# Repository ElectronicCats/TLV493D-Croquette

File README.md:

# Electronic Cats Croquette TLV493D

The 3D magnetic sensor TLV493D-A1B6 offers accurate three-dimensional sensing with extremely low power consumption in a small 6-pin package. With its magnetic field detection in x, y, and z-direction the sensor reliably measures three-dimensional, linear and rotation movements. Applications include joysticks, control elements (white goods, multifunction knops), or electric meters (anti tampering) and any other application that requires accurate angular measurements or low power consumptions.
The integrated temperature sensor can furthermore be used for plausibility checks.

Key features are 3D magnetic sensing with a very low power consumption during operations. The sensor has a digital output via 2-wire based standard I2C interface up to 1 MBit/sec and 12 bit data resolution for each measurement direction (Bx, By and Bz linear field measurement up to +-130mT).

## Key Features and Benefits
* Integrated temperature sensing
* Low current consumption of 0.007 µA in power down mode and 10 µA in ultra low power mode
* 2.7 to 3.5 V operating supply voltage
* Digital output via 2-wire standard I2C interface
* Bx, By and Bz linear field measurement up to ±130 mT
* 12-bit data resolution for each measurement direction
* Resolution 98 µT/LSB
* Operating temperature range from -40 °C to 125 °C
* [GUI](https://www.infineon.com/dgdl/Infineon-Software-for-3D-Magnetic-Sensor-2Go%20incl.%20out-of-shaft_05_06-SW-v05_06-EN.zip?fileId=5546d4626102d35a01614626f9644e4e) for free download as well as integration in Arduino IDE with this repository

## Usage

Please see the example sketches in the repository [Arduino Library](https://github.com/Infineon/TLV493D-A1B6-3DMagnetic-Sensor) in this library to learn more about the usage of the sensor.

### Usage Electronic Cats TLV493D with Arduino Library 

The Electronic Cats TLV493D-A1B6 3DMagnetic is a standalone break out board. You can connect it easily to any microcontroller of your choice which is Arduino compatible and has 3.3V logic level (please note that the Arduino UNO has 5V logic level and cannot be used without level shifting).

* [Link](https://github.com/Infineon/TLV493D-A1B6-3DMagnetic-Sensor/wiki) to the wiki with more information

### Processing
This library supports the open-source software [Processing](https://processing.org/) for creating GUIs. It allows you to connect your evaluation board to a PC over serial communication and visualisation of the embedded system. Find out more on the Arduino homepage [here](http://playground.arduino.cc/Interfacing/Processing). The respective files are stored in the /processing folder of this repository. 

### Printables
The TLx493D 3D magnetic sensor family has additional tools which can be directly mounted on top of the evaluation boards. The 3D print data of the [joystick](https://www.infineon.com/cms/en/product/promopages/sensors-2go/#Add-ons-3D-Magnetic-2GO), the [rotate knob](https://www.infineon.com/cms/en/product/promopages/sensors-2go/#Add-ons-3D-Magnetic-2GO) and the [linear slider](https://www.infineon.com/cms/en/product/promopages/sensors-2go/#Add-ons-3D-Magnetic-2GO) can be found in the folder `printables`.

## Board Information, Datasheet and Additional Information

The datasheet for the TLV493D-A1B6 can be found here [TLV493D-A1B6 Datasheet](https://www.infineon.com/dgdl/Infineon-TLV493D-A1B6-DS-v01_00-EN.pdf?fileId=5546d462525dbac40152a6b85c760e80) while respective application notes are located here [Application Notes](https://www.infineon.com/dgdl/Infineon-TLV493D-A1B6_3DMagnetic-UM-v01_03-EN.pdf?fileId=5546d46261d5e6820161e75721903ddd).

## License

Electronic Cats invests time and resources providing this open source design, please support Electronic Cats and open-source hardware by purchasing products from Electronic Cats!

Designed by Electronic Cats.

Hardware released under an CERN Open Hardware Licence v1.2. See the LICENSE_HARDWARE file for more information.

Electronic Cats is a registered trademark, please do not use if you sell these PCBs.

28 August 2019

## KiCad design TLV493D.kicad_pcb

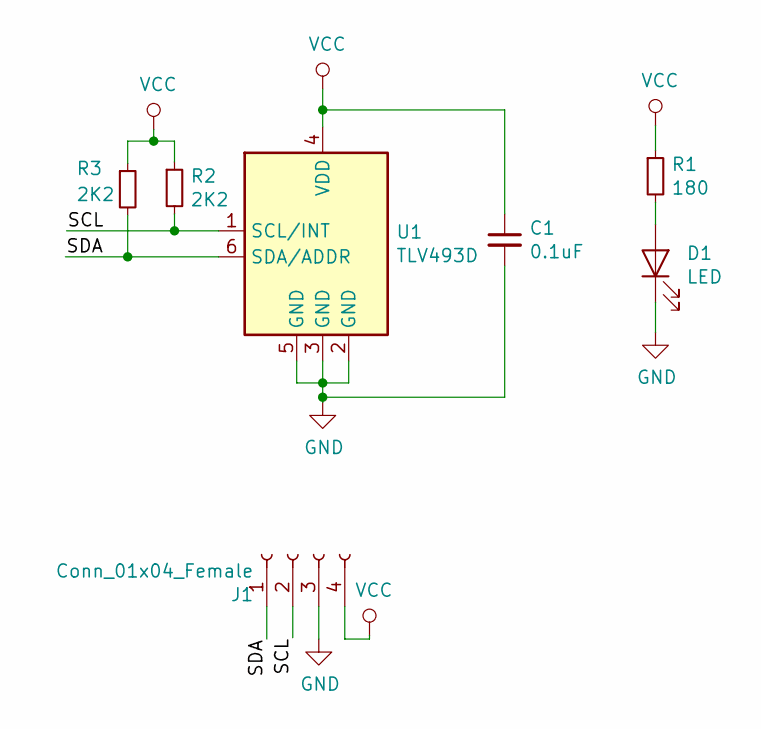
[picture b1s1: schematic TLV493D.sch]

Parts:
C1: 0.1uF; C_0805_2012Metric_Pad1.15x1.40mm_HandSolder
D1: LED; LED_0805_2012Metric_Pad1.15x1.40mm_HandSolder
J1: Conn_01x04_Female; PinHeader_1x04_P2.54mm_Vertical
R1: 180; R_0805_2012Metric_Pad1.15x1.40mm_HandSolder
R2, R3: 2K2; R_0805_2012Metric_Pad1.15x1.40mm_HandSolder
U1: TLV493D; TSOP-6_1.65x3.05mm_P0.95mm

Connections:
/SCL: J1.2, R2.2, U1.1 (SCL/INT)
/SDA: J1.1, R3.2, U1.6 (SDA/ADDR)
GND: C1.2, D1.1 (K), J1.3, U1.2 (GND), U1.3 (GND), U1.5 (GND)
unnamed: D1.2 (A), R1.2
VCC: C1.1, J1.4, R1.1, R2.1, R3.1, U1.4 (VDD)

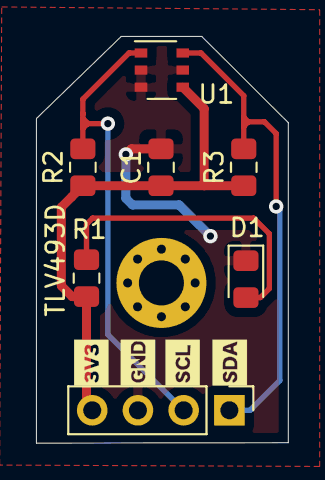
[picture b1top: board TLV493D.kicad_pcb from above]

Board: 2 copper layers, 14.0 x 22.6 mm, 7 parts (0 on the bottom side), 5 nets.

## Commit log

2019-08-28 Init schematic
2019-09-03 Update licenses
2019-09-04 Add connector
2019-09-05 Component order
2019-09-05 rotate pcb
2019-09-05 contour
2019-09-05 fix edge
2019-09-05 fix contour
2019-09-06 update edge
2019-09-06 update margin rect
2019-09-06 Routeo
2019-09-06 component number
2019-09-06 add hole M2, add logos and resize edge
2019-09-06 re routeo
2019-09-06 VCC,GND,SCL,SDA
2019-09-06 name change conector
2019-09-06 Change j1
2019-09-09 update tags
2019-09-10 Change R1,R2,R3 and add footprint manf
2019-09-10 fix components
2019-09-10 fix components and desing rules
2019-09-10 Update names and GND
2019-09-10 Corrections routeo
2019-12-17 new sizes
2019-12-17 add ignore
2019-12-18 fix countour
2019-12-18 Fix logos
2019-12-20 Routeo witout GND
2019-12-20 plane of GND
2019-12-20 Change capacitor footprint
